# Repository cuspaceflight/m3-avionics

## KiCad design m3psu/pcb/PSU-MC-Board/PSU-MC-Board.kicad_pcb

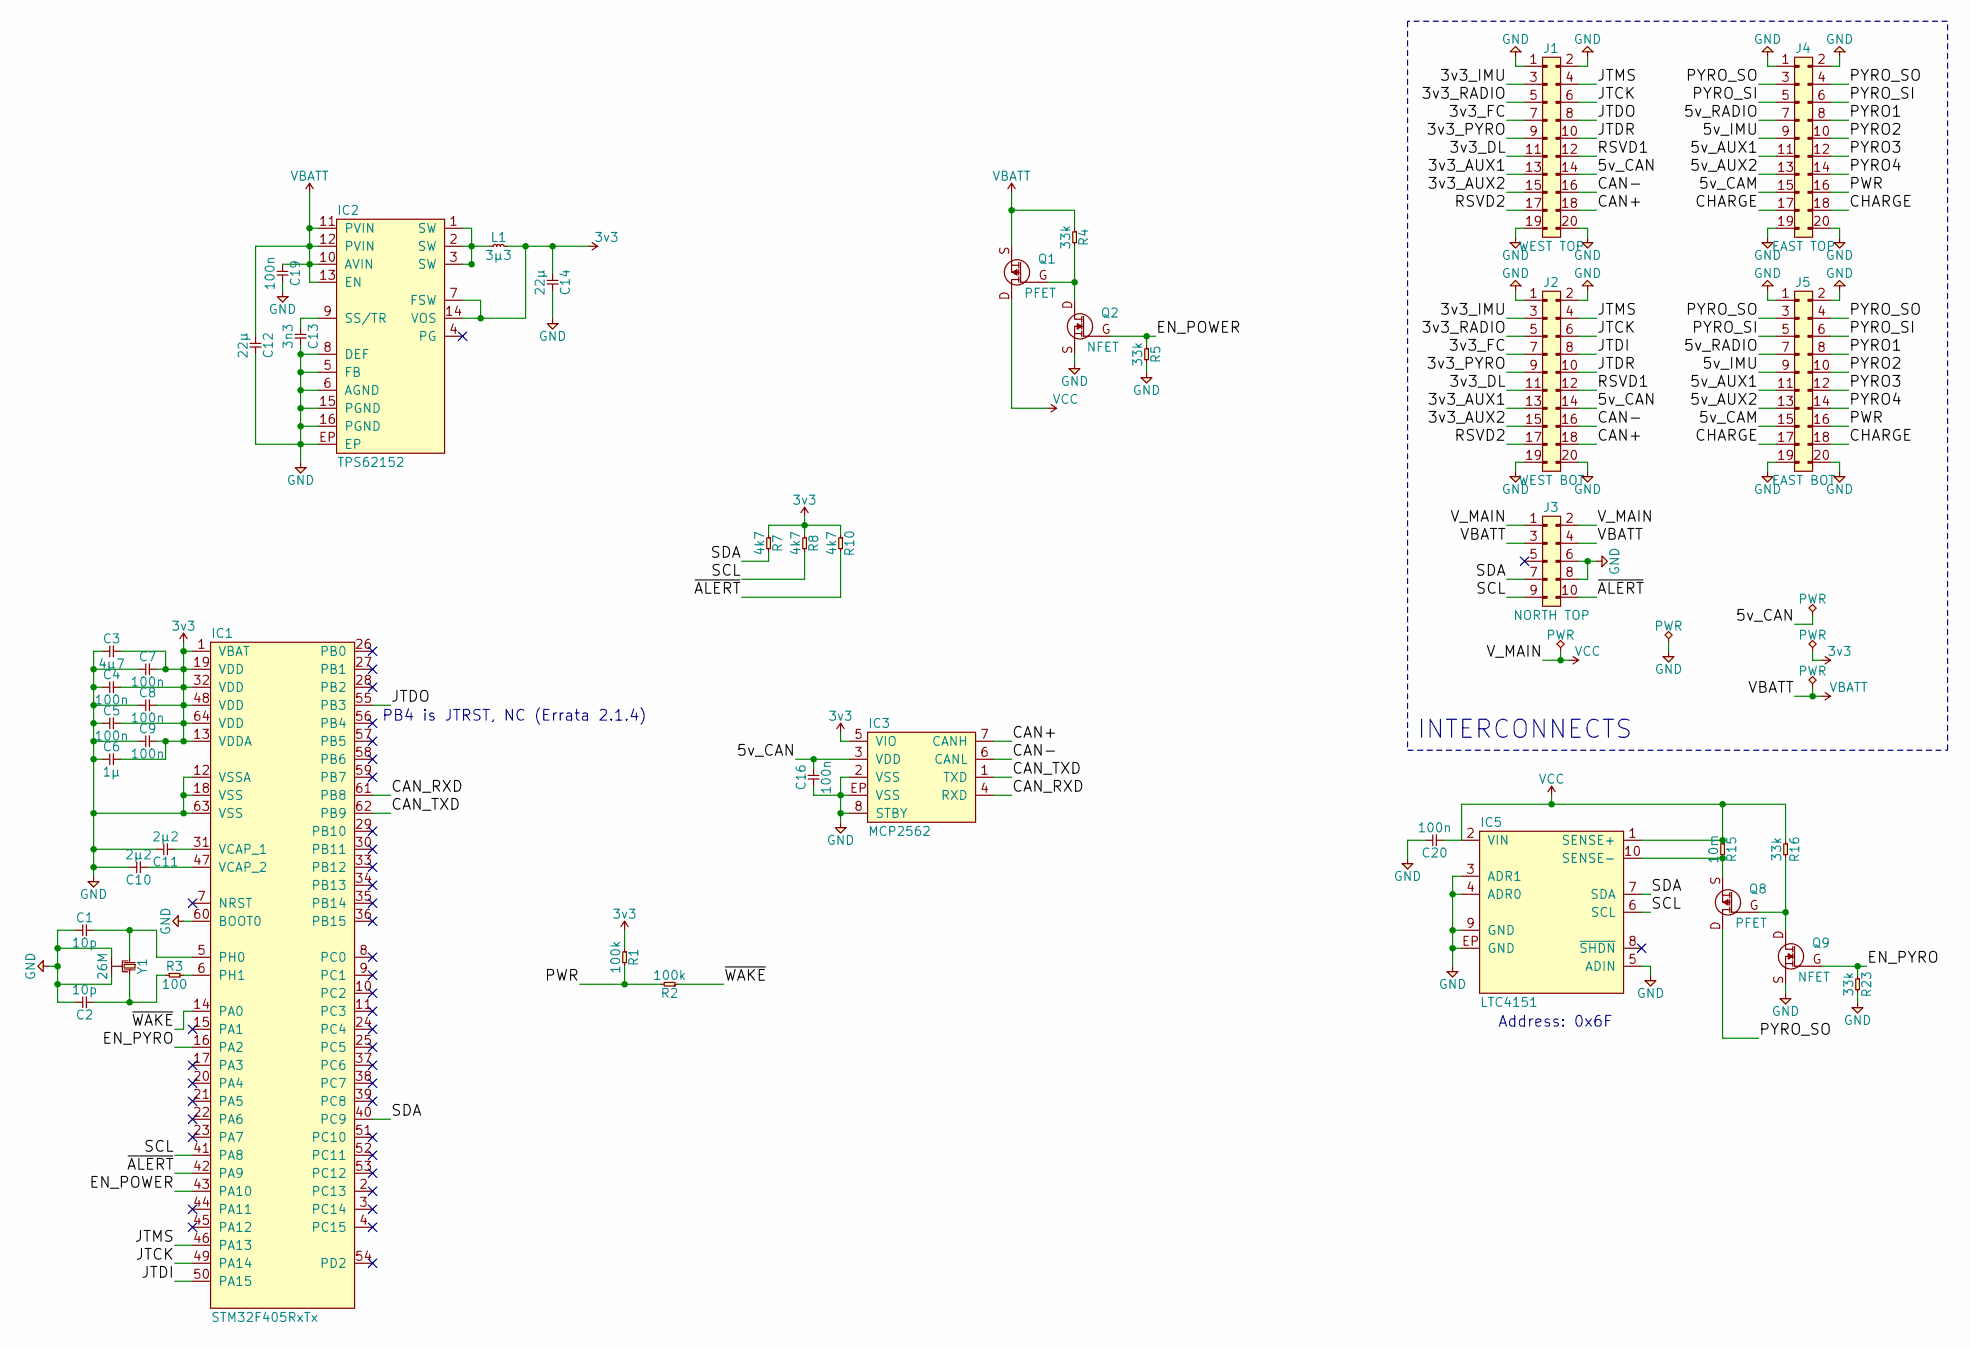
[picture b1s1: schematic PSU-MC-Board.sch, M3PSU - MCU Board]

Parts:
C1, C2: 10p; 0402; Farnell 2496790
C3: 4µ7; 0402; Farnell 2426952
C4, C5, C7, C8, C9, C16, C19, C20: 100n; 0402; Farnell 2496771
C6: 1µ; 0402; Farnell 2496814
C10, C11: 2µ2; 0402; Farnell 2362088
C12, C14: 22µ; 0805; Farnell 1907510
C13: 3n3; 0402; Farnell 1758918
IC1: STM32F405RxTx; LQFP-64; Farnell 2064363
IC2: TPS62152; QFN-16-EP-TI; Farnell 2382918
IC3: MCP2562; DFN-8-EP-MICROCHIP; Farnell 2448755
IC5: LTC4151; DFN-10-EP-LT; Farnell 2295457
J1: WEST TOP; TFML-110-02-L-D
J2: WEST BOT; SFML-110-02-L-D-LC
J3: NORTH TOP; TFML-105-02-L-D
J4: EAST TOP; TFML-110-02-L-D
J5: EAST BOT; SFML-110-02-L-D-LC
L1: 3µ3; VLS201610HBX-1; Farnell 2455373
Q1, Q8: PFET; SON2x2; Farnell 2501102
Q2, Q9: NFET; SOT-883-B; Farnell 2498598
R1, R2: 100k; 0402; Farnell 9239472
R3: 100; 0402; Farnell 9239111
R4, R5, R16, R23: 33k; 0402; Farnell 2447160
R7, R8, R10: 4k7; 0402; Farnell 2447187
R15: 10m; 0805; Farnell 2503034
Y1: 26M; XTAL-20x16; Farnell 2506952

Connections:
3v3: C3.2, C4.2, C5.2, C6.2, C7.2, C8.2, C9.2, C14.1, IC1.1 (VBAT), IC1.13 (VDDA), IC1.19 (VDD), IC1.32 (VDD), IC1.48 (VDD), IC1.64 (VDD), IC2.7 (FSW), IC2.14 (VOS), IC3.5 (VIO), L1.2, R1.1, R7.1, R8.1, R10.1
/3v3_AUX1: J1.13, J2.13
/3v3_AUX2: J1.15, J2.15
/3v3_DL: J1.11, J2.11
/3v3_FC: J1.7, J2.7
/3v3_IMU: J1.3, J2.3
/3v3_PYRO: J1.9, J2.9
/3v3_RADIO: J1.5, J2.5
/5v_AUX1: J4.11, J5.11
/5v_AUX2: J4.13, J5.13
/5v_CAM: J4.15, J5.15
/5v_CAN: C16.1, IC3.3 (VDD), J1.14, J2.14
/5v_IMU: J4.9, J5.9
/5v_RADIO: J4.7, J5.7
/CAN+: IC3.7 (CANH), J1.18, J2.18
/CAN-: IC3.6 (CANL), J1.16, J2.16
/CAN_RXD: IC1.61 (PB8), IC3.4 (RXD)
/CAN_TXD: IC1.62 (PB9), IC3.1 (TXD)
/CHARGE: J4.17, J4.18, J5.17, J5.18
/EN_POWER: IC1.43 (PA10), Q2.G, R5.1
/EN_PYRO: IC1.16 (PA2), Q9.G, R23.1
/JTCK: IC1.49 (PA14), J1.6, J2.6
/JTDI: IC1.50 (PA15), J2.8
/JTDO: IC1.55 (PB3), J1.8
/JTDR: J1.10, J2.10
/JTMS: IC1.46 (PA13), J1.4, J2.4
/PWR: J4.16, J5.16, R1.2, R2.2
/PYRO1: J4.8, J5.8
/PYRO2: J4.10, J5.10
/PYRO3: J4.12, J5.12
/PYRO4: J4.14, J5.14
/PYRO_SI: J4.5, J4.6, J5.5, J5.6
/PYRO_SO: J4.3, J4.4, J5.3, J5.4, Q8.D
/RSVD1: J1.12, J2.12
/RSVD2: J1.17, J2.17
/SCL: IC1.41 (PA8), IC5.6 (SCL), J3.9, R8.2
/SDA: IC1.40 (PC9), IC5.7 (SDA), J3.7, R7.2
/~ALERT: IC1.42 (PA9), J3.10, R10.2
/~WAKE: IC1.14 (PA0), R2.1
GND: C1.1, C2.2, C3.1, C4.1, C5.1, C6.1, C7.1, C8.1, C9.1, C10.2, C11.2, C12.2, C13.2, C14.2, C16.2, C19.2, C20.2, IC1.12 (VSSA), IC1.18 (VSS), IC1.60 (BOOT0), IC1.63 (VSS), IC2.5 (FB), IC2.6 (AGND), IC2.8 (DEF), IC2.15 (PGND), IC2.16 (PGND), IC2.EP, IC3.2 (VSS), IC3.8 (STBY), IC3.EP (VSS), IC5.3 (ADR1), IC5.4 (ADR0), IC5.5 (ADIN), IC5.9 (GND), IC5.EP (GND), J1.1, J1.2, J1.19, J1.20, J2.1, J2.2, J2.19, J2.20, J3.6, J3.8, J4.1, J4.2, J4.19, J4.20, J5.1, J5.2, J5.19, J5.20, Q2.S, Q9.S, R5.2, R23.2, Y1.2, Y1.4
unnamed: C1.2, IC1.5 (PH0), Y1.1
unnamed: C2.1, R3.1, Y1.3
unnamed: C10.1, IC1.47 (VCAP_2)
unnamed: C11.1, IC1.31 (VCAP_1)
unnamed: C13.1, IC2.9 (SS/TR)
unnamed: IC1.6 (PH1), R3.2
unnamed: IC2.1 (SW), IC2.2 (SW), IC2.3 (SW), L1.1
unnamed: IC5.10 (SENSE-), Q8.S, R15.2
unnamed: Q1.G, Q2.D, R4.2
unnamed: Q8.G, Q9.D, R16.2
VBATT: C12.1, C19.1, IC2.10 (AVIN), IC2.11 (PVIN), IC2.12 (PVIN), IC2.13 (EN), J3.3, J3.4, Q1.S, R4.1
VCC: C20.1, IC5.1 (SENSE+), IC5.2 (VIN), J3.1, J3.2, Q1.D, R15.1, R16.1

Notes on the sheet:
PB4 is JTRST, NC (Errata 2.1.4)
Address: 0x6F
INTERCONNECTS

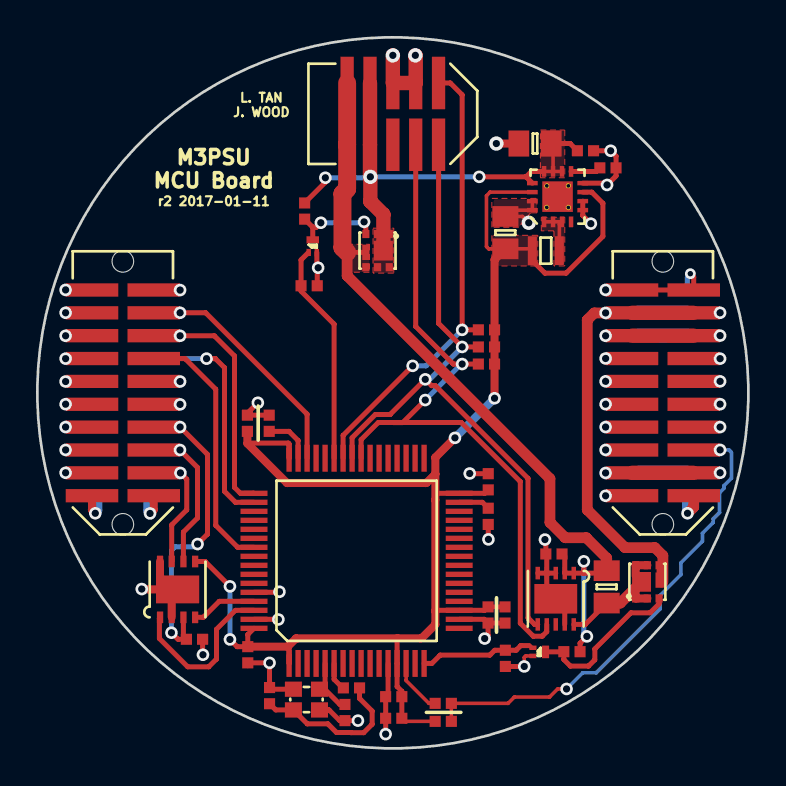
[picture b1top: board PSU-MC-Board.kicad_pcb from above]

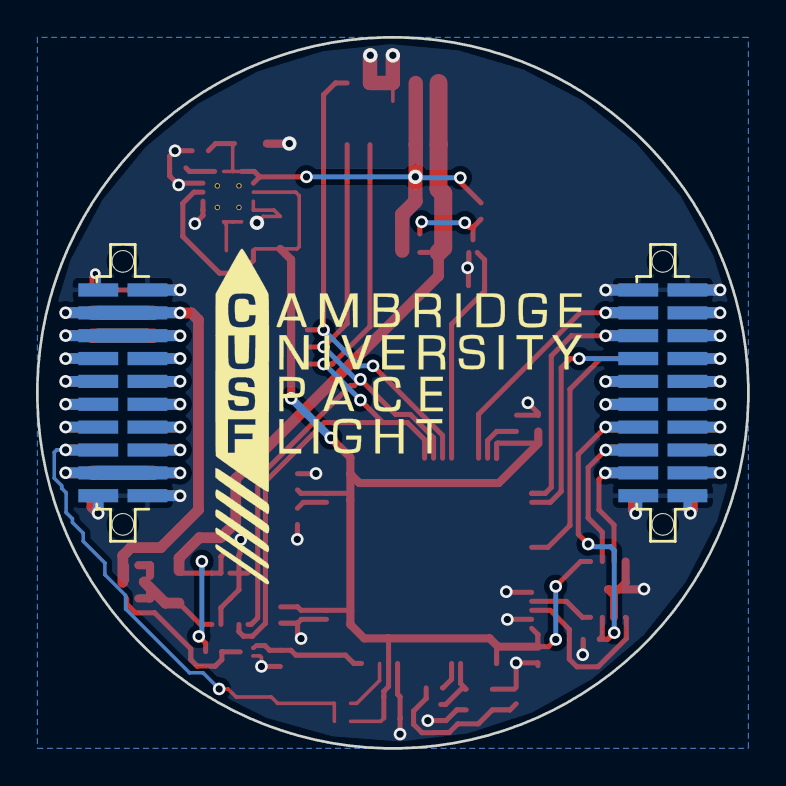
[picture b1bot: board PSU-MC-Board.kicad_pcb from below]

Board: 2 copper layers, 39.5 x 39.5 mm, 43 parts (2 on the bottom side), 52 nets.

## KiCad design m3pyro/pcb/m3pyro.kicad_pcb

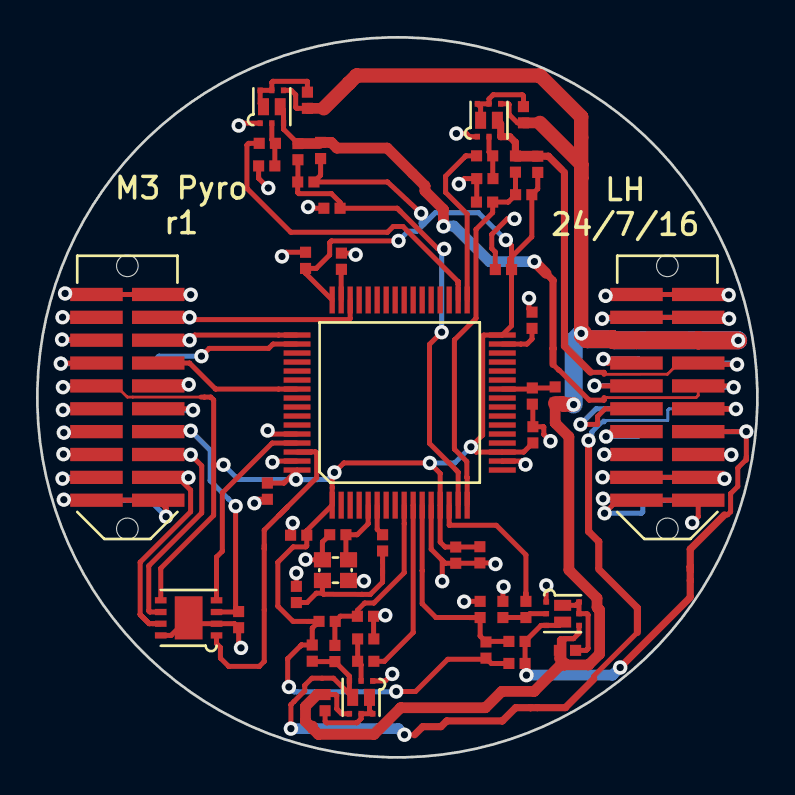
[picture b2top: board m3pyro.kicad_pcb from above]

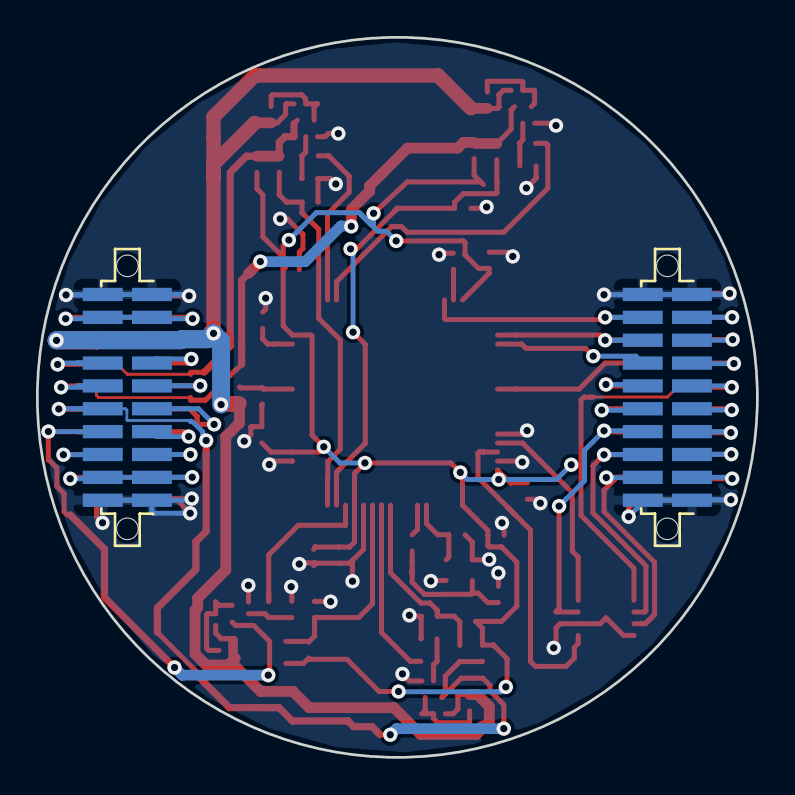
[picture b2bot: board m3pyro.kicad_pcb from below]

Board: 2 copper layers, 40.0 x 40.0 mm, 54 parts (2 on the bottom side), 55 nets.

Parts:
C1, C2, C3, C4, C8, C9, C11, C12, C13, C16: 100n; 0402
C5, C6: 10p; 0402
C7: 4µ7; 0402
C10: 1µ; 0402
C14, C15: 2µ2; 0402
D1, D2, D3, D4: D; 0402
IC1: STM32F405RxTx; LQFP-64
IC2: MCP2562; DFN-8-EP-MICROCHIP
J9: WEST TOP; TFML-110-02-L-D
J10: WEST BOT; SFML-110-02-L-D-LC
J11: EAST TOP; TFML-110-02-L-D
J12: EAST BOT; SFML-110-02-L-D-LC
Q1, Q2, Q3, Q4: 2FET3; PowerPAK-SC-70-6-DUAL
R1, R5, R8, R9, R10, R11, R12, R13, R14, R15, R16, R17: 10k; 0402
R2, R3, R4, R7: 1k; 0402
R6, R18, R19, R20, R25: 100; 0402
R26: 11; 0402
R27: 8; 0402
Y1: 26M; XTAL-20x16

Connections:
3v3: C7.2, C8.2, C9.2, C10.2, C11.2, C12.2, C13.2, D1.1, D2.1, D3.1, D4.1, IC1.1, IC1.13, IC1.19, IC1.32, IC1.48, IC1.64, IC2.5, J9.9, J10.9, R2.1, R3.1, R4.1, R7.1
/3v3_AUX1: J9.13, J10.13
/3v3_AUX2: J9.15, J10.15
/3v3_DL: J9.11, J10.11
/3v3_FC: J9.7, J10.7
/3v3_IMU: J9.3, J10.3
/3v3_RADIO: J9.5, J10.5
/5v_AUX1: J11.11, J12.11
/5v_AUX2: J11.13, J12.13
/5v_CAM: J11.15, J12.15
/5v_CAN: C16.1, IC2.3, J9.14, J10.14
/5v_IMU: J11.9, J12.9
/5v_RADIO: J11.7, J12.7
/CAN+: IC2.7, J9.18, J10.18
/CAN-: IC2.6, J9.16, J10.16
/CAN_RXD: IC1.61, IC2.4
/CAN_TXD: IC1.62, IC2.1
/CHARGE: J11.17, J11.18, J12.17, J12.18
/FIRE1: IC1.33, R6.2
/FIRE2: IC1.34, R18.2
/FIRE3: IC1.10, R19.2
/FIRE4: IC1.14, R20.2
/JTCK: IC1.49, J9.6, J10.6
/JTDI: IC1.50, J10.8
/JTDO: IC1.55, J9.8
/JTDR: J9.10, J10.10
/JTMS: IC1.46, J9.4, J10.4
/PWR: J11.16, J12.16
/PYRO1_BOT: J11.8, J12.8, Q1.D2, R2.2, R9.1
/PYRO1_RESISTANCE: C2.1, D2.2, IC1.16, R9.2
/PYRO2_BOT: J11.10, J12.10, Q2.D2, R3.2, R15.1
/PYRO2_RESISTANCE: C1.1, D1.2, IC1.15, R15.2
/PYRO3_BOT: J11.12, J12.12, Q3.D2, R4.2, R16.1
/PYRO3_RESISTANCE: C3.1, D3.2, IC1.9, R16.2
/PYRO4_BOT: J11.14, J12.14, Q4.D2, R7.2, R17.1
/PYRO4_RESISTANCE: C4.1, D4.2, IC1.11, R17.2
/PYRO_SI: J11.5, J11.6, J12.5, J12.6, Q1.S2, Q2.S2, Q3.S2, Q4.S2, R1.1, R8.1, R10.1, R11.1, R26.1
/PYRO_SO: J11.3, J11.4, J12.3, J12.4
/RSVD1: J9.12, J10.12
/RSVD2: J9.17, J10.17
GND: C1.2, C2.2, C3.2, C4.2, C5.1, C6.2, C7.1, C8.1, C9.1, C10.1, C11.1, C12.1, C13.1, C14.2, C15.2, C16.2, IC1.12, IC1.18, IC1.60, IC1.63, IC2.2, IC2.8, IC2.EP, J9.1, J9.2, J9.19, J9.20, J10.1, J10.2, J10.19, J10.20, J11.1, J11.2, J11.19, J11.20, J12.1, J12.2, J12.19, J12.20, Q1.S1, Q2.S1, Q3.S1, Q4.S1, R5.2, R12.2, R13.2, R14.2, R27.2, Y1.2, Y1.4
unnamed: C5.2, IC1.5, Y1.1
unnamed: C6.1, R25.1, Y1.3
unnamed: C14.1, IC1.47
unnamed: C15.1, IC1.31
unnamed: IC1.6, R25.2
unnamed: IC1.26, R26.2, R27.1
unnamed: Q1.D1, Q1.G2, R1.2
unnamed: Q1.G1, R5.1, R6.1
unnamed: Q2.D1, Q2.G2, R8.2
unnamed: Q2.G1, R12.1, R18.1
unnamed: Q3.D1, Q3.G2, R10.2
unnamed: Q3.G1, R13.1, R19.1
unnamed: Q4.D1, Q4.G2, R11.2
unnamed: Q4.G1, R14.1, R20.1
